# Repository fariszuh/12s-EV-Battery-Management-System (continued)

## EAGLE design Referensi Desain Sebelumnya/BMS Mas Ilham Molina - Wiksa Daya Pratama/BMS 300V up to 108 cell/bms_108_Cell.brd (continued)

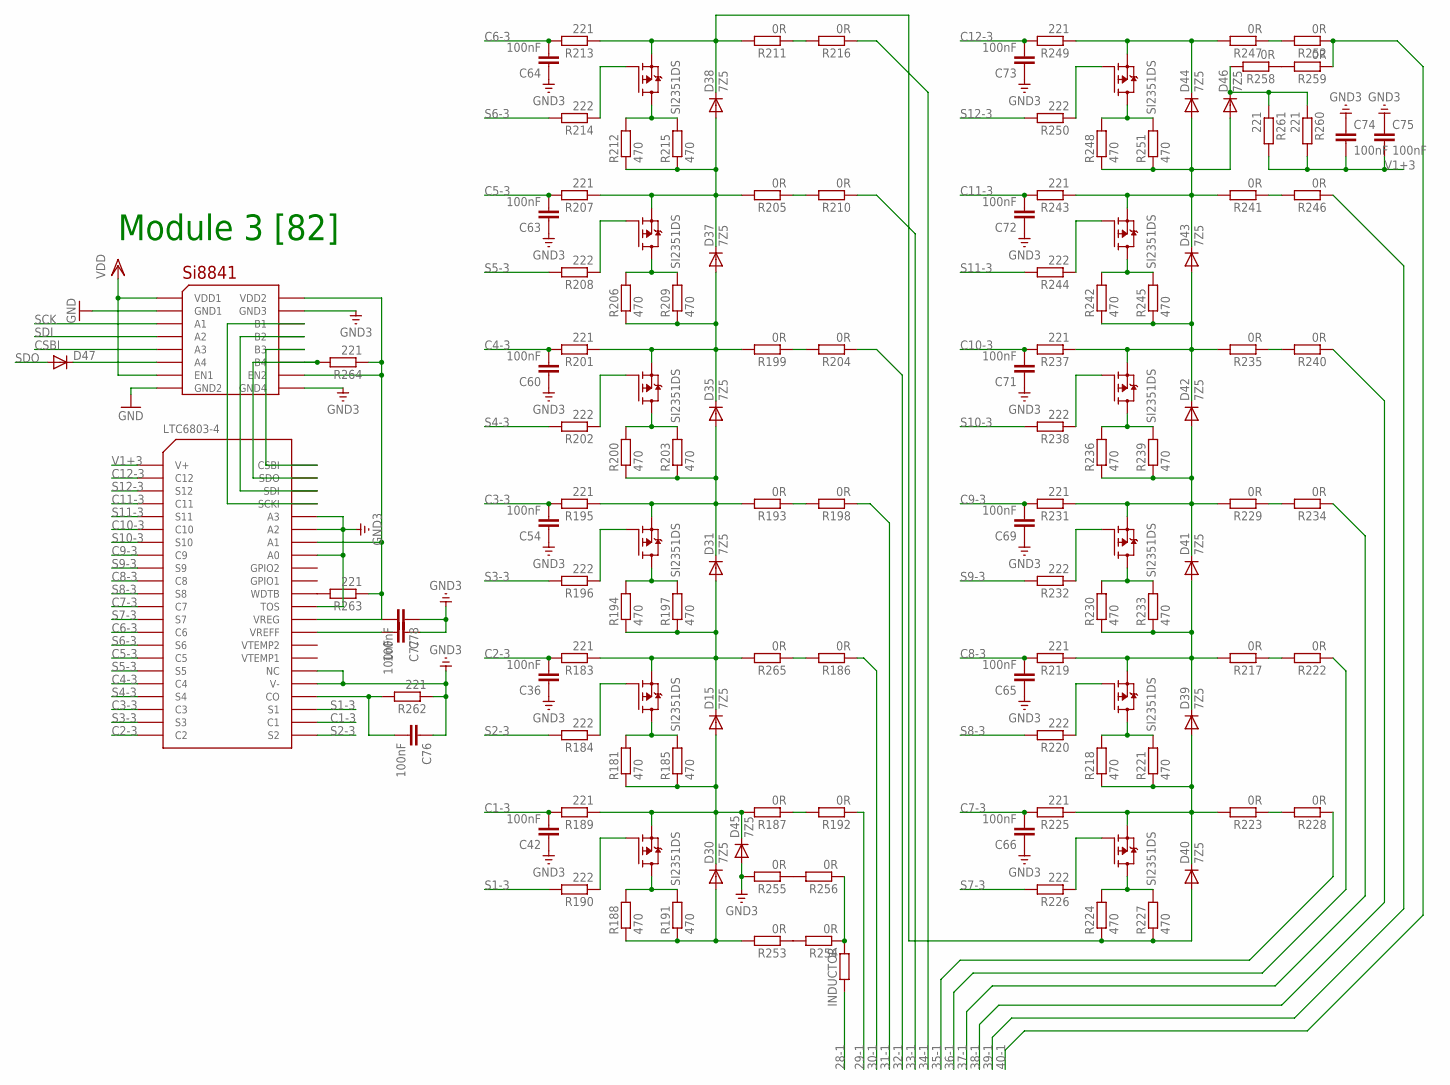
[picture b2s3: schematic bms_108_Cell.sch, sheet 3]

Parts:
C36, C42, C54, C60, C63, C64, C65, C66, C69, C71, C72, C73, C74, C75, C76, C77, C78: 100nF; C0805K
D15, D30, D31, D35, D37, D38, D39, D40, D41, D42, D43, D44, D45, D46: 7Z5; SMB
D47: DIODE-SOD123; SOD123
R181, R185, R188, R191, R194, R197, R200, R203, R206, R209, R212, R215, R218, R221, R224, R227, R230, R233, R236, R239, R242, R245, R248, R251: 470; R6332
R183, R189, R195, R201, R207, R213, R219, R225, R231, R237, R243, R249, R260, R261, R262, R263, R264: 221; R0805
R184, R190, R196, R202, R208, R214, R220, R226, R232, R238, R244, R250: 222; R0805
R186, R187, R192, R193, R198, R199, R204, R205, R210, R211, R216, R217, R222, R223, R228, R229, R234, R235, R240, R241, R246, R247, R252, R253, R254, R255, R256, R258, R259, R265: 0R; M1206
U$34: LTC6803-4; SSOP44
U$35: SI8841; SO16
U$36, U$37, U$38, U$39, U$40, U$41, U$42, U$45, U$46, U$47, U$48, U$49: SI2351DS; SOT23
U$50: INDUCTOR; L2012C

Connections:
28-1: U$50.2; also elsewhere on the board
29-1: R192.1; also elsewhere on the board
30-1: R186.1; also elsewhere on the board
31-1: R198.1; also elsewhere on the board
32-1: R204.1; also elsewhere on the board
33-1: R210.1; also elsewhere on the board
34-1: R216.1; also elsewhere on the board
35-1: R228.1; also elsewhere on the board
36-1: R222.1; also elsewhere on the board
37-1: R234.1; also elsewhere on the board
38-1: R240.1; also elsewhere on the board
39-1: R246.1; also elsewhere on the board
40-1: R252.1, R259.1; also elsewhere on the board
C1-3: C42.2, R189.2, U$34.24 (C1)
C2-3: C36.2, R183.2, U$34.P$22 (C2)
C3-3: C54.2, R195.2, U$34.P$20 (C3)
C4-3: C60.2, R201.2, U$34.P$18 (C4)
C5-3: C63.2, R207.2, U$34.P$16 (C5)
C6-3: C64.2, R213.2, U$34.P$14 (C6)
C7-3: C66.2, R225.2, U$34.P$12 (C7)
C8-3: C65.2, R219.2, U$34.P$10 (C8)
C9-3: C69.2, R231.2, U$34.P$8 (C9)
C10-3: C71.2, R237.2, U$34.P$6 (C10)
C11-3: C72.2, R243.2, U$34.P$4 (C11)
C12-3: C73.2, R249.2, U$34.P$2 (C12)
CSBI: U$35.5 (A3); also elsewhere on the board
GND: U$35.2 (GND1), U$35.8 (GND2); also elsewhere on the board
GND3: C36.1, C42.1, C54.1, C60.1, C63.1, C64.1, C65.1, C66.1, C69.1, C71.1, C72.1, C73.1, C74.1, C75.1, C76.1, C77.1, C78.1, D45.A, R255.2, R262.1, U$34.27 (V-), U$34.28 (NC), U$34.33 (TOS), U$34.37 (A0), U$34.39 (A2), U$34.40 (A3), U$35.9 (GND4), U$35.15 (GND3)
unnamed: R184.1, U$36.1 (G)
unnamed: R181.2, R185.2, U$36.3 (D)
unnamed: D15.A, D30.C, D45.C, R181.1, R185.1, R187.2, R189.1, U$37.2 (S)
unnamed: R186.2, R265.1
unnamed: R190.1, U$37.1 (G)
unnamed: R188.2, R191.2, U$37.3 (D)
unnamed: R187.1, R192.2
unnamed: R196.1, U$38.1 (G)
unnamed: R194.2, R197.2, U$38.3 (D)
unnamed: D15.C, D31.A, R183.1, R194.1, R197.1, R265.2, U$36.2 (S)
unnamed: R193.1, R198.2
unnamed: R202.1, U$39.1 (G)
unnamed: R200.2, R203.2, U$39.3 (D)
unnamed: D31.C, D35.A, R193.2, R195.1, R200.1, R203.1, U$38.2 (S)
unnamed: R199.1, R204.2
unnamed: R208.1, U$40.1 (G)
unnamed: R206.2, R209.2, U$40.3 (D)
unnamed: D35.C, D37.A, R199.2, R201.1, R206.1, R209.1, U$39.2 (S)
unnamed: R205.1, R210.2
unnamed: R214.1, U$41.1 (G)
unnamed: R212.2, R215.2, U$41.3 (D)
unnamed: D37.C, D38.A, R205.2, R207.1, R212.1, R215.1, U$40.2 (S)
unnamed: R211.1, R216.2
unnamed: R220.1, U$42.1 (G)
unnamed: R218.2, R221.2, U$42.3 (D)
unnamed: D39.A, D40.C, R218.1, R221.1, R223.2, R225.1, U$45.2 (S)
unnamed: R217.1, R222.2
unnamed: R226.1, U$45.1 (G)
unnamed: R224.2, R227.2, U$45.3 (D)
unnamed: D38.C, D40.A, R211.2, R213.1, R224.1, R227.1, U$41.2 (S)
unnamed: R223.1, R228.2
unnamed: R232.1, U$46.1 (G)
unnamed: R230.2, R233.2, U$46.3 (D)
unnamed: D39.C, D41.A, R217.2, R219.1, R230.1, R233.1, U$42.2 (S)
unnamed: R229.1, R234.2
unnamed: R238.1, U$47.1 (G)
unnamed: R236.2, R239.2, U$47.3 (D)
unnamed: D41.C, D42.A, R229.2, R231.1, R236.1, R239.1, U$46.2 (S)
unnamed: R235.1, R240.2
unnamed: R244.1, U$48.1 (G)
unnamed: R242.2, R245.2, U$48.3 (D)
unnamed: D42.C, D43.A, R235.2, R237.1, R242.1, R245.1, U$47.2 (S)
unnamed: R241.1, R246.2
unnamed: D44.C, R247.2, R249.1, U$49.2 (S)
unnamed: R250.1, U$49.1 (G)
unnamed: R248.2, R251.2, U$49.3 (D)
unnamed: D43.C, D44.A, D46.A, R241.2, R243.1, R248.1, R251.1, U$48.2 (S)
unnamed: R247.1, R252.2
unnamed: R253.1, R254.2
unnamed: R254.1, R256.1, U$50.1
unnamed: D30.A, R188.1, R191.1, R253.2
unnamed: R255.1, R256.2
unnamed: R258.1, R259.2
unnamed: D46.C, R258.2, R260.1, R261.1
unnamed: C76.2, R262.2, U$34.26 (CO)
unnamed: C77.2, U$34.31 (VREFF)
unnamed: C78.2, R263.1, R264.1, U$34.32 (VREG), U$34.38 (A1), U$35.10 (EN2), U$35.16 (VDD2)
unnamed: R263.2, U$34.34 (WDTB)
unnamed: R264.2, U$34.43 (SDO), U$35.11 (B4)
unnamed: U$34.44 (CSBI), U$35.12 (B3)
unnamed: U$34.42 (SDI), U$35.13 (B2)
unnamed: U$34.41 (SCKI), U$35.14 (B1)
unnamed: D47.C, U$35.6 (A4)
S1-3: R190.2, U$34.25 (S1)
S2-3: R184.2, U$34.23 (S2)
S3-3: R196.2, U$34.P$21 (S3)
S4-3: R202.2, U$34.P$19 (S4)
S5-3: R208.2, U$34.P$17 (S5)
S6-3: R214.2, U$34.P$15 (S6)
S7-3: R226.2, U$34.P$13 (S7)
S8-3: R220.2, U$34.P$11 (S8)
S9-3: R232.2, U$34.P$9 (S9)
S10-3: R238.2, U$34.P$7 (S10)
S11-3: R244.2, U$34.P$5 (S11)
S12-3: R250.2, U$34.P$3 (S12)
SCK: U$35.3 (A1); also elsewhere on the board
SDI: U$35.4 (A2); also elsewhere on the board
SDO: D47.A; also elsewhere on the board
V1+3: C74.2, C75.2, R260.2, R261.2, U$34.P$1 (V+)
VDD: U$35.1 (VDD1), U$35.7 (EN1); also elsewhere on the board

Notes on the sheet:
Module 3 [82]

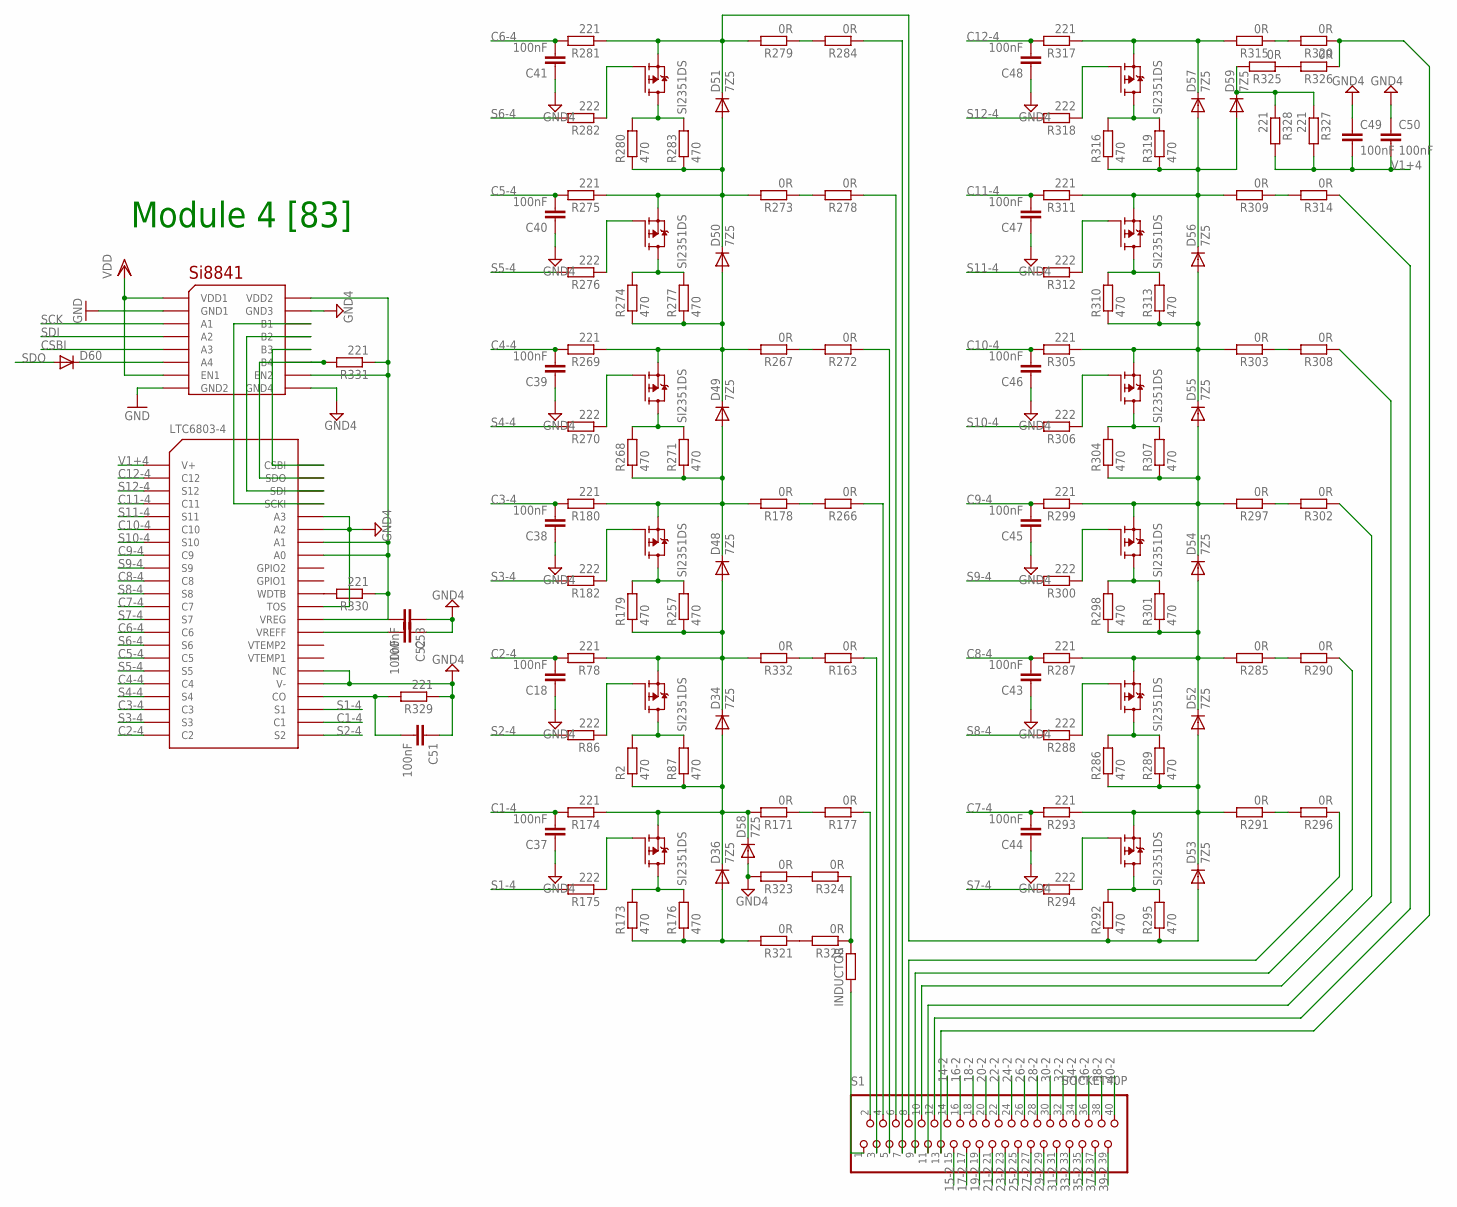
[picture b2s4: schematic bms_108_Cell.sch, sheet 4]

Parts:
C18, C37, C38, C39, C40, C41, C43, C44, C45, C46, C47, C48, C49, C50, C51, C52, C53: 100nF; C0805K
D34, D36, D48, D49, D50, D51, D52, D53, D54, D55, D56, D57, D58, D59: 7Z5; SMB
D60: DIODE-SOD123; SOD123
R2, R87, R173, R176, R179, R257, R268, R271, R274, R277, R280, R283, R286, R289, R292, R295, R298, R301, R304, R307, R310, R313, R316, R319: 470; R6332
R78, R174, R180, R269, R275, R281, R287, R293, R299, R305, R311, R317, R327, R328, R329, R330, R331: 221; R0805
R86, R175, R182, R270, R276, R282, R288, R294, R300, R306, R312, R318: 222; R0805
R163, R171, R177, R178, R266, R267, R272, R273, R278, R279, R284, R285, R290, R291, R296, R297, R302, R303, R308, R309, R314, R315, R320, R321, R322, R323, R324, R325, R326, R332: 0R; M1206
S1: SOCKET40P; 40PIN
U$31: LTC6803-4; SSOP44
U$32: SI8841; SO16
U$33, U$43, U$44, U$51, U$52, U$53, U$54, U$55, U$56, U$57, U$58, U$59: SI2351DS; SOT23
U$60: INDUCTOR; L2012C

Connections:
14-2: S1.14; also elsewhere on the board
15-2: S1.15; also elsewhere on the board
16-2: S1.16; also elsewhere on the board
17-2: S1.17; also elsewhere on the board
18-2: S1.18; also elsewhere on the board
19-2: S1.19; also elsewhere on the board
20-2: S1.20; also elsewhere on the board
21-2: S1.21; also elsewhere on the board
22-2: S1.22; also elsewhere on the board
23-2: S1.23; also elsewhere on the board
24-2: S1.24; also elsewhere on the board
25-2: S1.25; also elsewhere on the board
26-2: S1.26; also elsewhere on the board
27-2: S1.27
28-2: S1.28; also elsewhere on the board
29-2: S1.29; also elsewhere on the board
30-2: S1.30; also elsewhere on the board
31-2: S1.31; also elsewhere on the board
32-2: S1.32; also elsewhere on the board
33-2: S1.33; also elsewhere on the board
34-2: S1.34; also elsewhere on the board
35-2: S1.35; also elsewhere on the board
36-2: S1.36; also elsewhere on the board
37-2: S1.37; also elsewhere on the board
38-2: S1.38; also elsewhere on the board
39-2: S1.39; also elsewhere on the board
40-2: S1.40; also elsewhere on the board
C1-4: C37.2, R174.2, U$31.24 (C1)
C2-4: C18.2, R78.2, U$31.P$22 (C2)
C3-4: C38.2, R180.2, U$31.P$20 (C3)
C4-4: C39.2, R269.2, U$31.P$18 (C4)
C5-4: C40.2, R275.2, U$31.P$16 (C5)
C6-4: C41.2, R281.2, U$31.P$14 (C6)
C7-4: C44.2, R293.2, U$31.P$12 (C7)
C8-4: C43.2, R287.2, U$31.P$10 (C8)
C9-4: C45.2, R299.2, U$31.P$8 (C9)
C10-4: C46.2, R305.2, U$31.P$6 (C10)
C11-4: C47.2, R311.2, U$31.P$4 (C11)
C12-4: C48.2, R317.2, U$31.P$2 (C12)
CSBI: U$32.5 (A3); also elsewhere on the board
GND: U$32.2 (GND1), U$32.8 (GND2); also elsewhere on the board
GND4: C18.1, C37.1, C38.1, C39.1, C40.1, C41.1, C43.1, C44.1, C45.1, C46.1, C47.1, C48.1, C49.1, C50.1, C51.1, C52.1, C53.1, D58.A, R323.2, R329.1, U$31.27 (V-), U$31.28 (NC), U$31.33 (TOS), U$31.39 (A2), U$31.40 (A3), U$32.9 (GND4), U$32.15 (GND3)
unnamed: R86.1, U$33.1 (G)
unnamed: R2.2, R87.2, U$33.3 (D)
unnamed: D34.A, D36.C, D58.C, R2.1, R87.1, R171.2, R174.1, U$43.2 (S)
unnamed: R163.2, R332.1
unnamed: R175.1, U$43.1 (G)
unnamed: R173.2, R176.2, U$43.3 (D)
unnamed: R171.1, R177.2
unnamed: R182.1, U$44.1 (G)
unnamed: R179.2, R257.2, U$44.3 (D)
unnamed: D34.C, D48.A, R78.1, R179.1, R257.1, R332.2, U$33.2 (S)
unnamed: R178.1, R266.2
unnamed: R270.1, U$51.1 (G)
unnamed: R268.2, R271.2, U$51.3 (D)
unnamed: D48.C, D49.A, R178.2, R180.1, R268.1, R271.1, U$44.2 (S)
unnamed: R267.1, R272.2
unnamed: R276.1, U$52.1 (G)
unnamed: R274.2, R277.2, U$52.3 (D)
unnamed: D49.C, D50.A, R267.2, R269.1, R274.1, R277.1, U$51.2 (S)
unnamed: R273.1, R278.2
unnamed: R282.1, U$53.1 (G)
unnamed: R280.2, R283.2, U$53.3 (D)
unnamed: D50.C, D51.A, R273.2, R275.1, R280.1, R283.1, U$52.2 (S)
unnamed: R279.1, R284.2
unnamed: R288.1, U$54.1 (G)
unnamed: R286.2, R289.2, U$54.3 (D)
unnamed: D52.A, D53.C, R286.1, R289.1, R291.2, R293.1, U$55.2 (S)
unnamed: R285.1, R290.2
unnamed: R294.1, U$55.1 (G)
unnamed: R292.2, R295.2, U$55.3 (D)
unnamed: D51.C, D53.A, R279.2, R281.1, R292.1, R295.1, U$53.2 (S)
unnamed: R291.1, R296.2
unnamed: R300.1, U$56.1 (G)
unnamed: R298.2, R301.2, U$56.3 (D)
unnamed: D52.C, D54.A, R285.2, R287.1, R298.1, R301.1, U$54.2 (S)
unnamed: R297.1, R302.2
unnamed: R306.1, U$57.1 (G)
unnamed: R304.2, R307.2, U$57.3 (D)
unnamed: D54.C, D55.A, R297.2, R299.1, R304.1, R307.1, U$56.2 (S)
unnamed: R303.1, R308.2
unnamed: R312.1, U$58.1 (G)
unnamed: R310.2, R313.2, U$58.3 (D)
unnamed: D55.C, D56.A, R303.2, R305.1, R310.1, R313.1, U$57.2 (S)
unnamed: R309.1, R314.2
unnamed: D57.C, R315.2, R317.1, U$59.2 (S)
unnamed: R318.1, U$59.1 (G)
unnamed: R316.2, R319.2, U$59.3 (D)
unnamed: D56.C, D57.A, D59.A, R309.2, R311.1, R316.1, R319.1, U$58.2 (S)
unnamed: R315.1, R320.2
unnamed: R321.1, R322.2
unnamed: R322.1, R324.1, U$60.1
unnamed: D36.A, R173.1, R176.1, R321.2
unnamed: R323.1, R324.2
unnamed: R325.1, R326.2
unnamed: D59.C, R325.2, R327.1, R328.1
unnamed: R320.1, R326.1, S1.13
unnamed: C51.2, R329.2, U$31.26 (CO)
unnamed: C52.2, U$31.31 (VREFF)
unnamed: C53.2, R330.1, R331.1, U$31.32 (VREG), U$31.37 (A0), U$31.38 (A1), U$32.10 (EN2), U$32.16 (VDD2)
unnamed: R330.2, U$31.34 (WDTB)
unnamed: R331.2, U$31.43 (SDO), U$32.11 (B4)
unnamed: U$31.44 (CSBI), U$32.12 (B3)
unnamed: U$31.42 (SDI), U$32.13 (B2)
unnamed: U$31.41 (SCKI), U$32.14 (B1)
unnamed: S1.1, U$60.2
unnamed: R177.1, S1.2
unnamed: R163.1, S1.3
unnamed: R266.1, S1.4
unnamed: R272.1, S1.5
unnamed: R278.1, S1.6
unnamed: R284.1, S1.7
unnamed: R296.1, S1.8
unnamed: R290.1, S1.9
unnamed: R302.1, S1.10
unnamed: R308.1, S1.11
unnamed: R314.1, S1.12
unnamed: D60.C, U$32.6 (A4)
S1-4: R175.2, U$31.25 (S1)
S2-4: R86.2, U$31.23 (S2)
S3-4: R182.2, U$31.P$21 (S3)
S4-4: R270.2, U$31.P$19 (S4)
S5-4: R276.2, U$31.P$17 (S5)
S6-4: R282.2, U$31.P$15 (S6)
S7-4: R294.2, U$31.P$13 (S7)
S8-4: R288.2, U$31.P$11 (S8)
S9-4: R300.2, U$31.P$9 (S9)
S10-4: R306.2, U$31.P$7 (S10)
S11-4: R312.2, U$31.P$5 (S11)
S12-4: R318.2, U$31.P$3 (S12)
SCK: U$32.3 (A1); also elsewhere on the board
SDI: U$32.4 (A2); also elsewhere on the board
SDO: D60.A; also elsewhere on the board
V1+4: C49.2, C50.2, R327.2, R328.2, U$31.P$1 (V+)
VDD: U$32.1 (VDD1), U$32.7 (EN1); also elsewhere on the board

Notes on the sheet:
Module 4 [83]

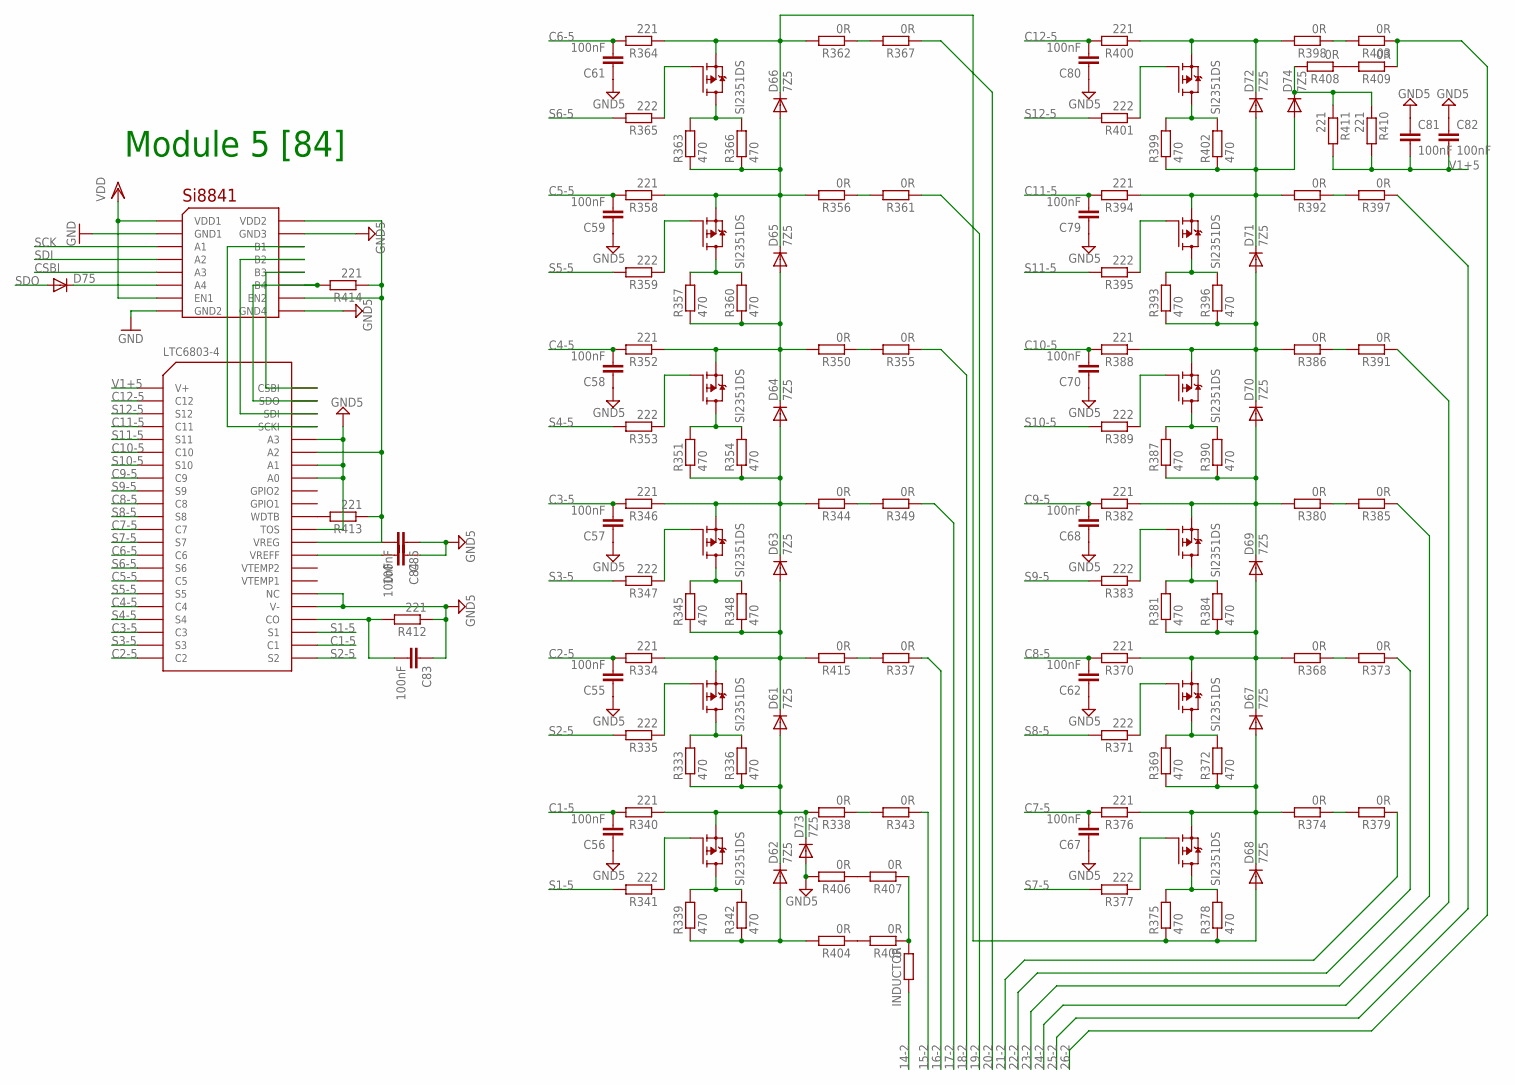
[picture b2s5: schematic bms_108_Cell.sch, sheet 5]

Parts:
C55, C56, C57, C58, C59, C61, C62, C67, C68, C70, C79, C80, C81, C82, C83, C84, C85: 100nF; C0805K
D61, D62, D63, D64, D65, D66, D67, D68, D69, D70, D71, D72, D73, D74: 7Z5; SMB
D75: DIODE-SOD123; SOD123
R333, R336, R339, R342, R345, R348, R351, R354, R357, R360, R363, R366, R369, R372, R375, R378, R381, R384, R387, R390, R393, R396, R399, R402: 470; R6332
R334, R340, R346, R352, R358, R364, R370, R376, R382, R388, R394, R400, R410, R411, R412, R413, R414: 221; R0805
R335, R341, R347, R353, R359, R365, R371, R377, R383, R389, R395, R401: 222; R0805
R337, R338, R343, R344, R349, R350, R355, R356, R361, R362, R367, R368, R373, R374, R379, R380, R385, R386, R391, R392, R397, R398, R403, R404, R405, R406, R407, R408, R409, R415: 0R; M1206
U$61: LTC6803-4; SSOP44
U$62: SI8841; SO16
U$63, U$64, U$65, U$66, U$67, U$68, U$69, U$70, U$71, U$72, U$73, U$74: SI2351DS; SOT23
U$75: INDUCTOR; L2012C

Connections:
14-2: U$75.2; also elsewhere on the board
15-2: R343.1; also elsewhere on the board
16-2: R337.1; also elsewhere on the board
17-2: R349.1; also elsewhere on the board
18-2: R355.1; also elsewhere on the board
19-2: R361.1; also elsewhere on the board
20-2: R367.1; also elsewhere on the board
21-2: R379.1; also elsewhere on the board
22-2: R373.1; also elsewhere on the board
23-2: R385.1; also elsewhere on the board
24-2: R391.1; also elsewhere on the board
25-2: R397.1; also elsewhere on the board
26-2: R403.1, R409.1; also elsewhere on the board
C1-5: C56.2, R340.2, U$61.24 (C1)
C2-5: C55.2, R334.2, U$61.P$22 (C2)
C3-5: C57.2, R346.2, U$61.P$20 (C3)
C4-5: C58.2, R352.2, U$61.P$18 (C4)
C5-5: C59.2, R358.2, U$61.P$16 (C5)
C6-5: C61.2, R364.2, U$61.P$14 (C6)
C7-5: C67.2, R376.2, U$61.P$12 (C7)
C8-5: C62.2, R370.2, U$61.P$10 (C8)
C9-5: C68.2, R382.2, U$61.P$8 (C9)
C10-5: C70.2, R388.2, U$61.P$6 (C10)
C11-5: C79.2, R394.2, U$61.P$4 (C11)
C12-5: C80.2, R400.2, U$61.P$2 (C12)
CSBI: U$62.5 (A3); also elsewhere on the board
GND: U$62.2 (GND1), U$62.8 (GND2); also elsewhere on the board
GND5: C55.1, C56.1, C57.1, C58.1, C59.1, C61.1, C62.1, C67.1, C68.1, C70.1, C79.1, C80.1, C81.1, C82.1, C83.1, C84.1, C85.1, D73.A, R406.2, R412.1, U$61.27 (V-), U$61.28 (NC), U$61.33 (TOS), U$61.37 (A0), U$61.38 (A1), U$61.40 (A3), U$62.9 (GND4), U$62.15 (GND3)
unnamed: R335.1, U$63.1 (G)
unnamed: R333.2, R336.2, U$63.3 (D)
unnamed: D61.A, D62.C, D73.C, R333.1, R336.1, R338.2, R340.1, U$64.2 (S)
unnamed: R337.2, R415.1
unnamed: R341.1, U$64.1 (G)
unnamed: R339.2, R342.2, U$64.3 (D)
unnamed: R338.1, R343.2
unnamed: R347.1, U$65.1 (G)
unnamed: R345.2, R348.2, U$65.3 (D)
unnamed: D61.C, D63.A, R334.1, R345.1, R348.1, R415.2, U$63.2 (S)
unnamed: R344.1, R349.2
unnamed: R353.1, U$66.1 (G)
unnamed: R351.2, R354.2, U$66.3 (D)
unnamed: D63.C, D64.A, R344.2, R346.1, R351.1, R354.1, U$65.2 (S)
unnamed: R350.1, R355.2
unnamed: R359.1, U$67.1 (G)
unnamed: R357.2, R360.2, U$67.3 (D)
unnamed: D64.C, D65.A, R350.2, R352.1, R357.1, R360.1, U$66.2 (S)
unnamed: R356.1, R361.2
unnamed: R365.1, U$68.1 (G)
unnamed: R363.2, R366.2, U$68.3 (D)
unnamed: D65.C, D66.A, R356.2, R358.1, R363.1, R366.1, U$67.2 (S)
unnamed: R362.1, R367.2
unnamed: R371.1, U$69.1 (G)
unnamed: R369.2, R372.2, U$69.3 (D)
unnamed: D67.A, D68.C, R369.1, R372.1, R374.2, R376.1, U$70.2 (S)
unnamed: R368.1, R373.2
unnamed: R377.1, U$70.1 (G)
unnamed: R375.2, R378.2, U$70.3 (D)
unnamed: D66.C, D68.A, R362.2, R364.1, R375.1, R378.1, U$68.2 (S)
unnamed: R374.1, R379.2
unnamed: R383.1, U$71.1 (G)
unnamed: R381.2, R384.2, U$71.3 (D)
unnamed: D67.C, D69.A, R368.2, R370.1, R381.1, R384.1, U$69.2 (S)
unnamed: R380.1, R385.2
unnamed: R389.1, U$72.1 (G)
unnamed: R387.2, R390.2, U$72.3 (D)
unnamed: D69.C, D70.A, R380.2, R382.1, R387.1, R390.1, U$71.2 (S)
unnamed: R386.1, R391.2
unnamed: R395.1, U$73.1 (G)
unnamed: R393.2, R396.2, U$73.3 (D)
unnamed: D70.C, D71.A, R386.2, R388.1, R393.1, R396.1, U$72.2 (S)
unnamed: R392.1, R397.2
unnamed: D72.C, R398.2, R400.1, U$74.2 (S)
unnamed: R401.1, U$74.1 (G)
unnamed: R399.2, R402.2, U$74.3 (D)
unnamed: D71.C, D72.A, D74.A, R392.2, R394.1, R399.1, R402.1, U$73.2 (S)
unnamed: R398.1, R403.2
unnamed: R404.1, R405.2
unnamed: R405.1, R407.1, U$75.1
unnamed: D62.A, R339.1, R342.1, R404.2
unnamed: R406.1, R407.2
unnamed: R408.1, R409.2
unnamed: D74.C, R408.2, R410.1, R411.1
unnamed: C83.2, R412.2, U$61.26 (CO)
unnamed: C84.2, U$61.31 (VREFF)
unnamed: C85.2, R413.1, R414.1, U$61.32 (VREG), U$61.39 (A2), U$62.10 (EN2), U$62.16 (VDD2)
unnamed: R413.2, U$61.34 (WDTB)
unnamed: R414.2, U$61.43 (SDO), U$62.11 (B4)
unnamed: U$61.44 (CSBI), U$62.12 (B3)
unnamed: U$61.42 (SDI), U$62.13 (B2)
unnamed: U$61.41 (SCKI), U$62.14 (B1)
unnamed: D75.C, U$62.6 (A4)
S1-5: R341.2, U$61.25 (S1)
S2-5: R335.2, U$61.23 (S2)
S3-5: R347.2, U$61.P$21 (S3)
S4-5: R353.2, U$61.P$19 (S4)
S5-5: R359.2, U$61.P$17 (S5)
S6-5: R365.2, U$61.P$15 (S6)
S7-5: R377.2, U$61.P$13 (S7)
S8-5: R371.2, U$61.P$11 (S8)
S9-5: R383.2, U$61.P$9 (S9)
S10-5: R389.2, U$61.P$7 (S10)
S11-5: R395.2, U$61.P$5 (S11)
S12-5: R401.2, U$61.P$3 (S12)
SCK: U$62.3 (A1); also elsewhere on the board
SDI: U$62.4 (A2); also elsewhere on the board
SDO: D75.A; also elsewhere on the board
V1+5: C81.2, C82.2, R410.2, R411.2, U$61.P$1 (V+)
VDD: U$62.1 (VDD1), U$62.7 (EN1); also elsewhere on the board

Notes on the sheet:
Module 5 [84]

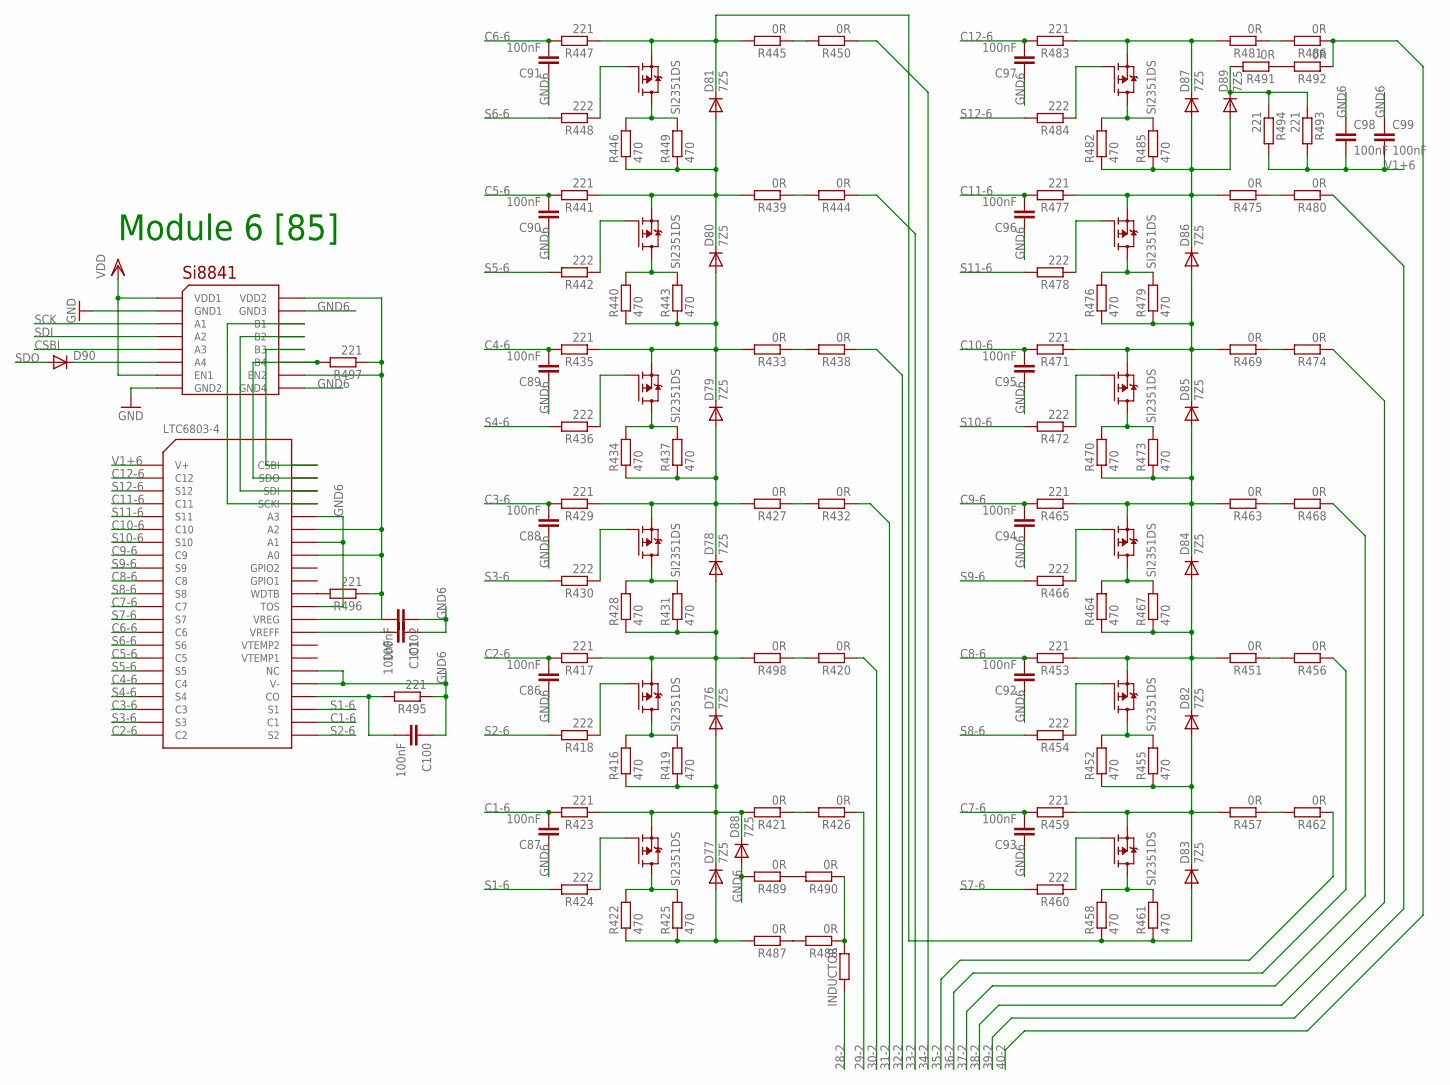
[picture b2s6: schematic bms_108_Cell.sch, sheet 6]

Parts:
C86, C87, C88, C89, C90, C91, C92, C93, C94, C95, C96, C97, C98, C99, C100, C101, C102: 100nF; C0805K
D76, D77, D78, D79, D80, D81, D82, D83, D84, D85, D86, D87, D88, D89: 7Z5; SMB
D90: DIODE-SOD123; SOD123
R416, R419, R422, R425, R428, R431, R434, R437, R440, R443, R446, R449, R452, R455, R458, R461, R464, R467, R470, R473, R476, R479, R482, R485: 470; R6332
R417, R423, R429, R435, R441, R447, R453, R459, R465, R471, R477, R483, R493, R494, R495, R496, R497: 221; R0805
R418, R424, R430, R436, R442, R448, R454, R460, R466, R472, R478, R484: 222; R0805
R420, R421, R426, R427, R432, R433, R438, R439, R444, R445, R450, R451, R456, R457, R462, R463, R468, R469, R474, R475, R480, R481, R486, R487, R488, R489, R490, R491, R492, R498: 0R; M1206
U$76: LTC6803-4; SSOP44
U$77: SI8841; SO16
U$78, U$79, U$80, U$81, U$82, U$83, U$84, U$85, U$86, U$87, U$88, U$89: SI2351DS; SOT23
U$90: INDUCTOR; L2012C

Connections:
28-2: U$90.2; also elsewhere on the board
29-2: R426.1; also elsewhere on the board
30-2: R420.1; also elsewhere on the board
31-2: R432.1; also elsewhere on the board
32-2: R438.1; also elsewhere on the board
33-2: R444.1; also elsewhere on the board
34-2: R450.1; also elsewhere on the board
35-2: R462.1; also elsewhere on the board
36-2: R456.1; also elsewhere on the board
37-2: R468.1; also elsewhere on the board
38-2: R474.1; also elsewhere on the board
39-2: R480.1; also elsewhere on the board
40-2: R486.1, R492.1; also elsewhere on the board
C1-6: C87.2, R423.2, U$76.24 (C1)
C2-6: C86.2, R417.2, U$76.P$22 (C2)
C3-6: C88.2, R429.2, U$76.P$20 (C3)
C4-6: C89.2, R435.2, U$76.P$18 (C4)
C5-6: C90.2, R441.2, U$76.P$16 (C5)
C6-6: C91.2, R447.2, U$76.P$14 (C6)
C7-6: C93.2, R459.2, U$76.P$12 (C7)
C8-6: C92.2, R453.2, U$76.P$10 (C8)
C9-6: C94.2, R465.2, U$76.P$8 (C9)
C10-6: C95.2, R471.2, U$76.P$6 (C10)
C11-6: C96.2, R477.2, U$76.P$4 (C11)
C12-6: C97.2, R483.2, U$76.P$2 (C12)
CSBI: U$77.5 (A3); also elsewhere on the board
GND: U$77.2 (GND1), U$77.8 (GND2); also elsewhere on the board
GND6: C86.1, C87.1, C88.1, C89.1, C90.1, C91.1, C92.1, C93.1, C94.1, C95.1, C96.1, C97.1, C98.1, C99.1, C100.1, C101.1, C102.1, D88.A, R489.2, R495.1, U$76.27 (V-), U$76.28 (NC), U$76.33 (TOS), U$76.38 (A1), U$76.40 (A3), U$77.9 (GND4), U$77.15 (GND3)
unnamed: R418.1, U$78.1 (G)
unnamed: R416.2, R419.2, U$78.3 (D)
unnamed: D76.A, D77.C, D88.C, R416.1, R419.1, R421.2, R423.1, U$79.2 (S)
unnamed: R420.2, R498.1
unnamed: R424.1, U$79.1 (G)
unnamed: R422.2, R425.2, U$79.3 (D)
unnamed: R421.1, R426.2
unnamed: R430.1, U$80.1 (G)
unnamed: R428.2, R431.2, U$80.3 (D)
unnamed: D76.C, D78.A, R417.1, R428.1, R431.1, R498.2, U$78.2 (S)
unnamed: R427.1, R432.2
unnamed: R436.1, U$81.1 (G)
unnamed: R434.2, R437.2, U$81.3 (D)
unnamed: D78.C, D79.A, R427.2, R429.1, R434.1, R437.1, U$80.2 (S)
unnamed: R433.1, R438.2
unnamed: R442.1, U$82.1 (G)
unnamed: R440.2, R443.2, U$82.3 (D)
unnamed: D79.C, D80.A, R433.2, R435.1, R440.1, R443.1, U$81.2 (S)
unnamed: R439.1, R444.2
unnamed: R448.1, U$83.1 (G)
unnamed: R446.2, R449.2, U$83.3 (D)
unnamed: D80.C, D81.A, R439.2, R441.1, R446.1, R449.1, U$82.2 (S)
unnamed: R445.1, R450.2
unnamed: R454.1, U$84.1 (G)
unnamed: R452.2, R455.2, U$84.3 (D)
unnamed: D82.A, D83.C, R452.1, R455.1, R457.2, R459.1, U$85.2 (S)
unnamed: R451.1, R456.2
unnamed: R460.1, U$85.1 (G)
unnamed: R458.2, R461.2, U$85.3 (D)
unnamed: D81.C, D83.A, R445.2, R447.1, R458.1, R461.1, U$83.2 (S)
unnamed: R457.1, R462.2
unnamed: R466.1, U$86.1 (G)
unnamed: R464.2, R467.2, U$86.3 (D)
unnamed: D82.C, D84.A, R451.2, R453.1, R464.1, R467.1, U$84.2 (S)
unnamed: R463.1, R468.2
unnamed: R472.1, U$87.1 (G)
unnamed: R470.2, R473.2, U$87.3 (D)
unnamed: D84.C, D85.A, R463.2, R465.1, R470.1, R473.1, U$86.2 (S)
unnamed: R469.1, R474.2
unnamed: R478.1, U$88.1 (G)
unnamed: R476.2, R479.2, U$88.3 (D)
unnamed: D85.C, D86.A, R469.2, R471.1, R476.1, R479.1, U$87.2 (S)
unnamed: R475.1, R480.2
unnamed: D87.C, R481.2, R483.1, U$89.2 (S)
unnamed: R484.1, U$89.1 (G)
unnamed: R482.2, R485.2, U$89.3 (D)
unnamed: D86.C, D87.A, D89.A, R475.2, R477.1, R482.1, R485.1, U$88.2 (S)
unnamed: R481.1, R486.2
unnamed: R487.1, R488.2
unnamed: R488.1, R490.1, U$90.1
unnamed: D77.A, R422.1, R425.1, R487.2
unnamed: R489.1, R490.2
unnamed: R491.1, R492.2
unnamed: D89.C, R491.2, R493.1, R494.1
unnamed: C100.2, R495.2, U$76.26 (CO)
unnamed: C101.2, U$76.31 (VREFF)
unnamed: C102.2, R496.1, R497.1, U$76.32 (VREG), U$76.37 (A0), U$76.39 (A2), U$77.10 (EN2), U$77.16 (VDD2)
unnamed: R496.2, U$76.34 (WDTB)
unnamed: R497.2, U$76.43 (SDO), U$77.11 (B4)
unnamed: U$76.44 (CSBI), U$77.12 (B3)
unnamed: U$76.42 (SDI), U$77.13 (B2)
unnamed: U$76.41 (SCKI), U$77.14 (B1)
unnamed: D90.C, U$77.6 (A4)
S1-6: R424.2, U$76.25 (S1)
S2-6: R418.2, U$76.23 (S2)
S3-6: R430.2, U$76.P$21 (S3)
S4-6: R436.2, U$76.P$19 (S4)
S5-6: R442.2, U$76.P$17 (S5)
S6-6: R448.2, U$76.P$15 (S6)
S7-6: R460.2, U$76.P$13 (S7)
S8-6: R454.2, U$76.P$11 (S8)
S9-6: R466.2, U$76.P$9 (S9)
S10-6: R472.2, U$76.P$7 (S10)
S11-6: R478.2, U$76.P$5 (S11)
S12-6: R484.2, U$76.P$3 (S12)
SCK: U$77.3 (A1); also elsewhere on the board
SDI: U$77.4 (A2); also elsewhere on the board
SDO: D90.A; also elsewhere on the board
V1+6: C98.2, C99.2, R493.2, R494.2, U$76.P$1 (V+)
VDD: U$77.1 (VDD1), U$77.7 (EN1); also elsewhere on the board

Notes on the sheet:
Module 6 [85]
